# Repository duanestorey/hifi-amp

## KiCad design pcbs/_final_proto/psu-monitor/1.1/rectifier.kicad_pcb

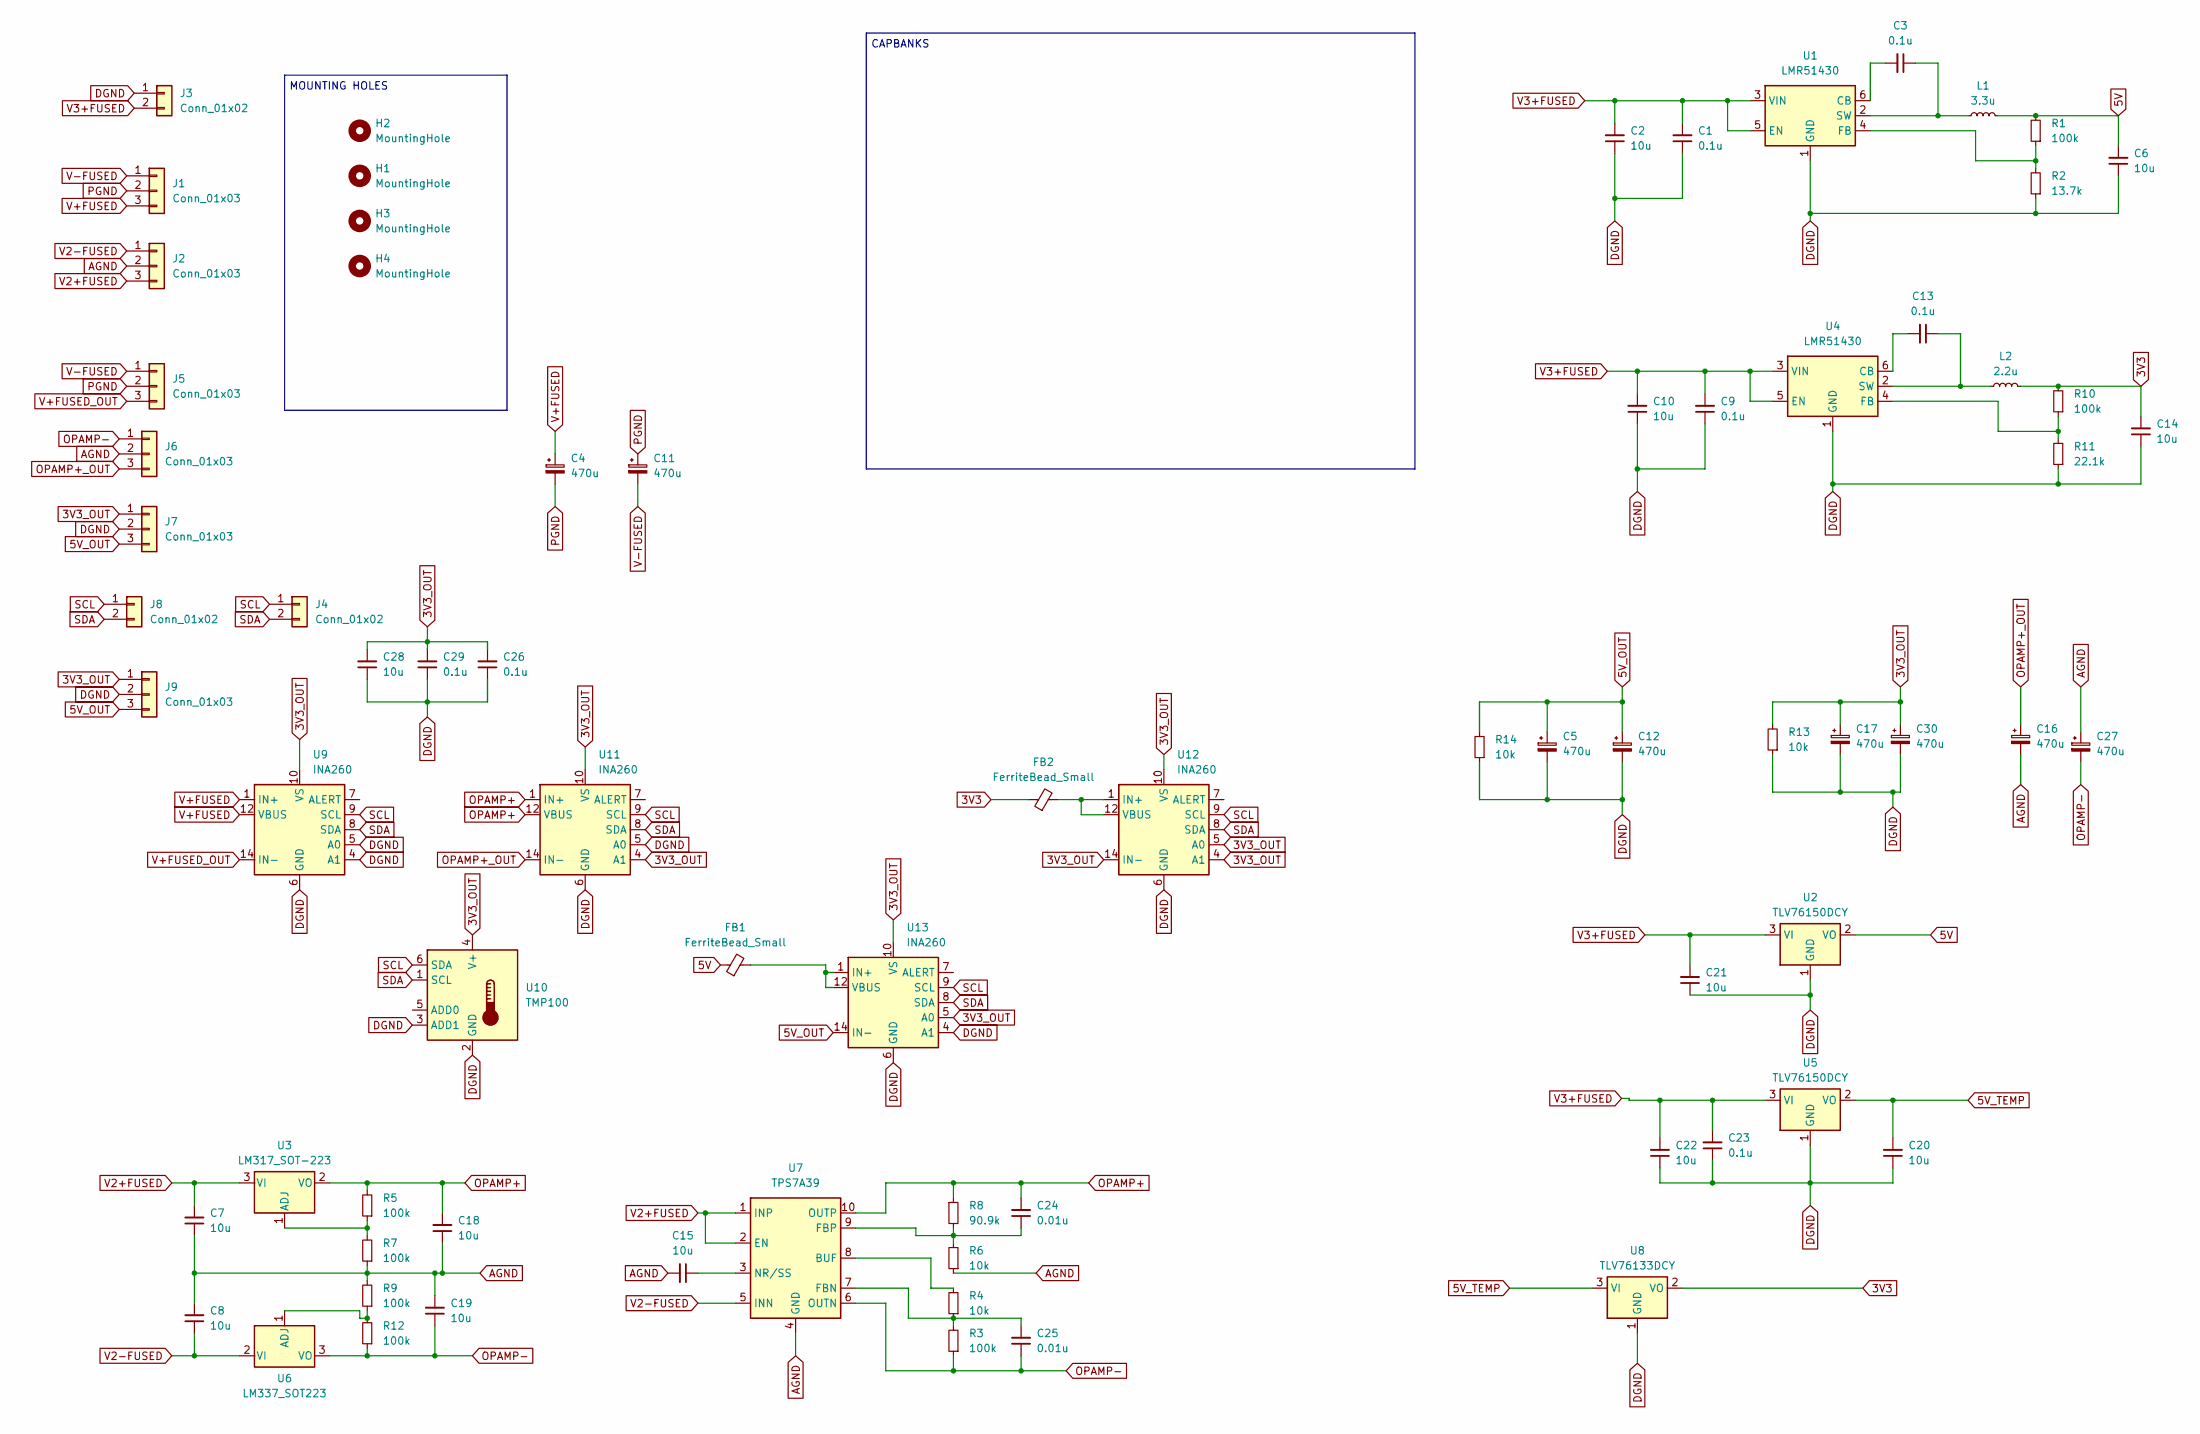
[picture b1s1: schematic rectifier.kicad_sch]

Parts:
C1, C3, C9, C13, C23, C26, C29: 0.1u; C_0805_2012Metric_Pad1.18x1.45mm_HandSolder_Duane
C2, C6, C7, C8, C10, C14, C15, C18, C19, C20, C21, C22, C28: 10u; C_1206_3216Metric_Pad1.33x1.80mm_HandSolder_Duane
C4, C5, C11, C12, C16, C17, C27, C30: 470u; CP_Elec_6.3x7.7
C24, C25: 0.01u; C_0805_2012Metric_Pad1.18x1.45mm_HandSolder_Duane
FB1, FB2: FerriteBead_Small; R_0805_2012Metric_Pad1.20x1.40mm_HandSolder_Duane
H1, H2, H3, H4: MountingHole; MountingHole_3.2mm_M3_DIN965_Pad_TopBottom
J1, J2, J5, J6, J7: Conn_01x03; JST_VH_B3P-VH-B_1x03_P3.96mm_Vertical_Duane
J3: Conn_01x02; JST_VH_B2P-VH-B_1x02_P3.96mm_Vertical_Duane
J4, J8: Conn_01x02; JST_PH_B2B-PH-K_1x02_P2.00mm_Vertical
J9: Conn_01x03; JST_PH_B3B-PH-K_1x03_P2.00mm_Vertical
L1: 3.3u; L_Wuerth_HCI-7030
L2: 2.2u; L_Wuerth_HCI-7030
R1, R3, R5, R7, R9, R10, R12: 100k; R_0805_2012Metric_Pad1.20x1.40mm_HandSolder_Duane
R2: 13.7k; R_0805_2012Metric_Pad1.20x1.40mm_HandSolder_Duane
R4, R6, R13, R14: 10k; R_0805_2012Metric_Pad1.20x1.40mm_HandSolder_Duane
R8: 90.9k; R_0805_2012Metric_Pad1.20x1.40mm_HandSolder_Duane
R11: 22.1k; R_0805_2012Metric_Pad1.20x1.40mm_HandSolder_Duane
U1, U4: LMR51430; SOT-23-6
U2, U5: TLV76150DCY; SOT-223-3_TabPin2
U3: LM317_SOT-223; SOT-223-3_TabPin2
U6: LM337_SOT223; SOT-223-3_TabPin2
U7: TPS7A39; Texas_S-PVSON-N10_ThermalVias
U8: TLV76133DCY; SOT-223-3_TabPin2
U9, U11, U12, U13: INA260; TSSOP-16_4.4x5mm_P0.65mm
U10: TMP100; SOT-23-6

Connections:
3V3: C14.2, FB2.1, L2.2, R10.2, U8.2 (VO)
3V3_OUT: C17.1, C26.2, C28.2, C29.2, C30.1, J7.1, J9.1, R13.2, U9.10 (VS), U10.4 (V+), U11.4 (A1), U11.10 (VS), U12.4 (A1), U12.5 (A0), U12.10 (VS), U12.14 (IN-), U12.15 (IN-), U12.16 (IN-), U13.5 (A0), U13.10 (VS)
5V: C6.2, FB1.1, L1.2, R1.2, U2.2 (VO)
5V_OUT: C5.1, C12.1, J7.3, J9.3, R14.2, U13.14 (IN-), U13.15 (IN-), U13.16 (IN-)
5V_TEMP: C20.2, U5.2 (VO), U8.3 (VI)
AGND: C7.1, C8.2, C15.2, C16.2, C18.1, C19.2, C27.1, J2.2, J6.2, R6.1, R7.1, R9.2, U7.4 (GND), U7.11 (GND)
DGND: C1.1, C2.1, C5.2, C6.1, C9.1, C10.1, C12.2, C14.1, C17.2, C20.1, C21.1, C22.1, C23.1, C26.1, C28.1, C29.1, C30.2, J3.1, J7.2, J9.2, R2.1, R11.1, R13.1, R14.1, U1.1 (GND), U2.1 (GND), U4.1 (GND), U5.1 (GND), U8.1 (GND), U9.4 (A1), U9.5 (A0), U9.6 (GND), U9.11 (GND), U10.2 (GND), U10.3 (ADD1), U11.5 (A0), U11.6 (GND), U11.11 (GND), U12.6 (GND), U12.11 (GND), U13.4 (A1), U13.6 (GND), U13.11 (GND)
unnamed: C3.2, U1.6 (CB)
unnamed: R1.1, R2.2, U1.4 (FB)
unnamed: C3.1, L1.1, U1.2 (SW)
unnamed: R5.1, R7.2, U3.1 (ADJ)
unnamed: C13.2, U4.6 (CB)
unnamed: R10.1, R11.2, U4.4 (FB)
unnamed: C13.1, L2.1, U4.2 (SW)
unnamed: R9.1, R12.2, U6.1 (ADJ)
unnamed: R4.2, U7.8 (BUF)
unnamed: C25.2, R3.2, R4.1, U7.7 (FBN)
unnamed: C24.1, R6.2, R8.2, U7.9 (FBP)
unnamed: C15.1, U7.3 (NR/SS)
unnamed: FB2.2, U12.1 (IN+), U12.2 (IN+), U12.3 (IN+), U12.12 (VBUS)
unnamed: FB1.2, U13.1 (IN+), U13.2 (IN+), U13.3 (IN+), U13.12 (VBUS)
OPAMP+: C18.2, C24.2, R5.2, R8.1, U3.2 (VO), U7.10 (OUTP), U11.1 (IN+), U11.2 (IN+), U11.3 (IN+), U11.12 (VBUS)
OPAMP+_OUT: C16.1, J6.3, U11.14 (IN-), U11.15 (IN-), U11.16 (IN-)
OPAMP-: C19.1, C25.1, C27.2, J6.1, R3.1, R12.1, U6.3 (VO), U7.6 (OUTN)
PGND: C4.2, C11.1, J1.2, J5.2
SCL: J4.1, J8.1, U9.9 (SCL), U10.6 (SDA), U11.9 (SCL), U12.9 (SCL), U13.9 (SCL)
SDA: J4.2, J8.2, U9.8 (SDA), U10.1 (SCL), U11.8 (SDA), U12.8 (SDA), U13.8 (SDA)
V2+FUSED: C7.2, J2.3, U3.3 (VI), U7.1 (INP), U7.2 (EN)
V2-FUSED: C8.1, J2.1, U6.2 (VI), U7.5 (INN)
V3+FUSED: C1.2, C2.2, C9.2, C10.2, C21.2, C22.2, C23.2, J3.2, U1.3 (VIN), U1.5 (EN), U2.3 (VI), U4.3 (VIN), U4.5 (EN), U5.3 (VI)
V+FUSED: C4.1, J1.3, U9.1 (IN+), U9.2 (IN+), U9.3 (IN+), U9.12 (VBUS)
V+FUSED_OUT: J5.3, U9.14 (IN-), U9.15 (IN-), U9.16 (IN-)
V-FUSED: C11.2, J1.1, J5.1

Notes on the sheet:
MOUNTING HOLES
CAPBANKS

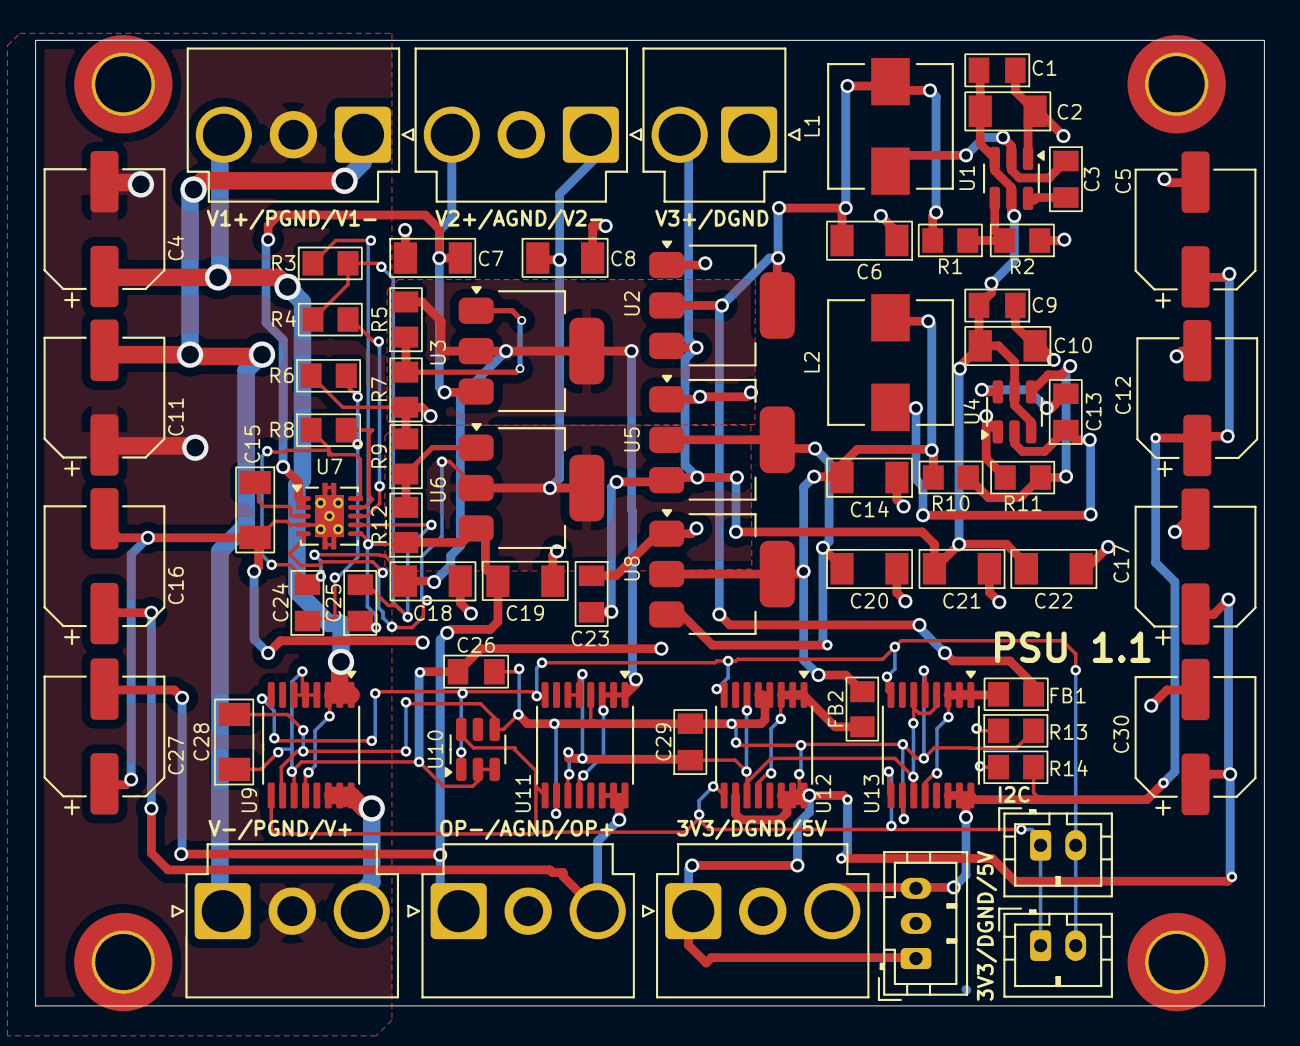
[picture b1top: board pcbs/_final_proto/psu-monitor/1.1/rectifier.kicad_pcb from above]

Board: 2 copper layers, 70.0 x 55.0 mm, 74 parts (0 on the bottom side), 33 nets.

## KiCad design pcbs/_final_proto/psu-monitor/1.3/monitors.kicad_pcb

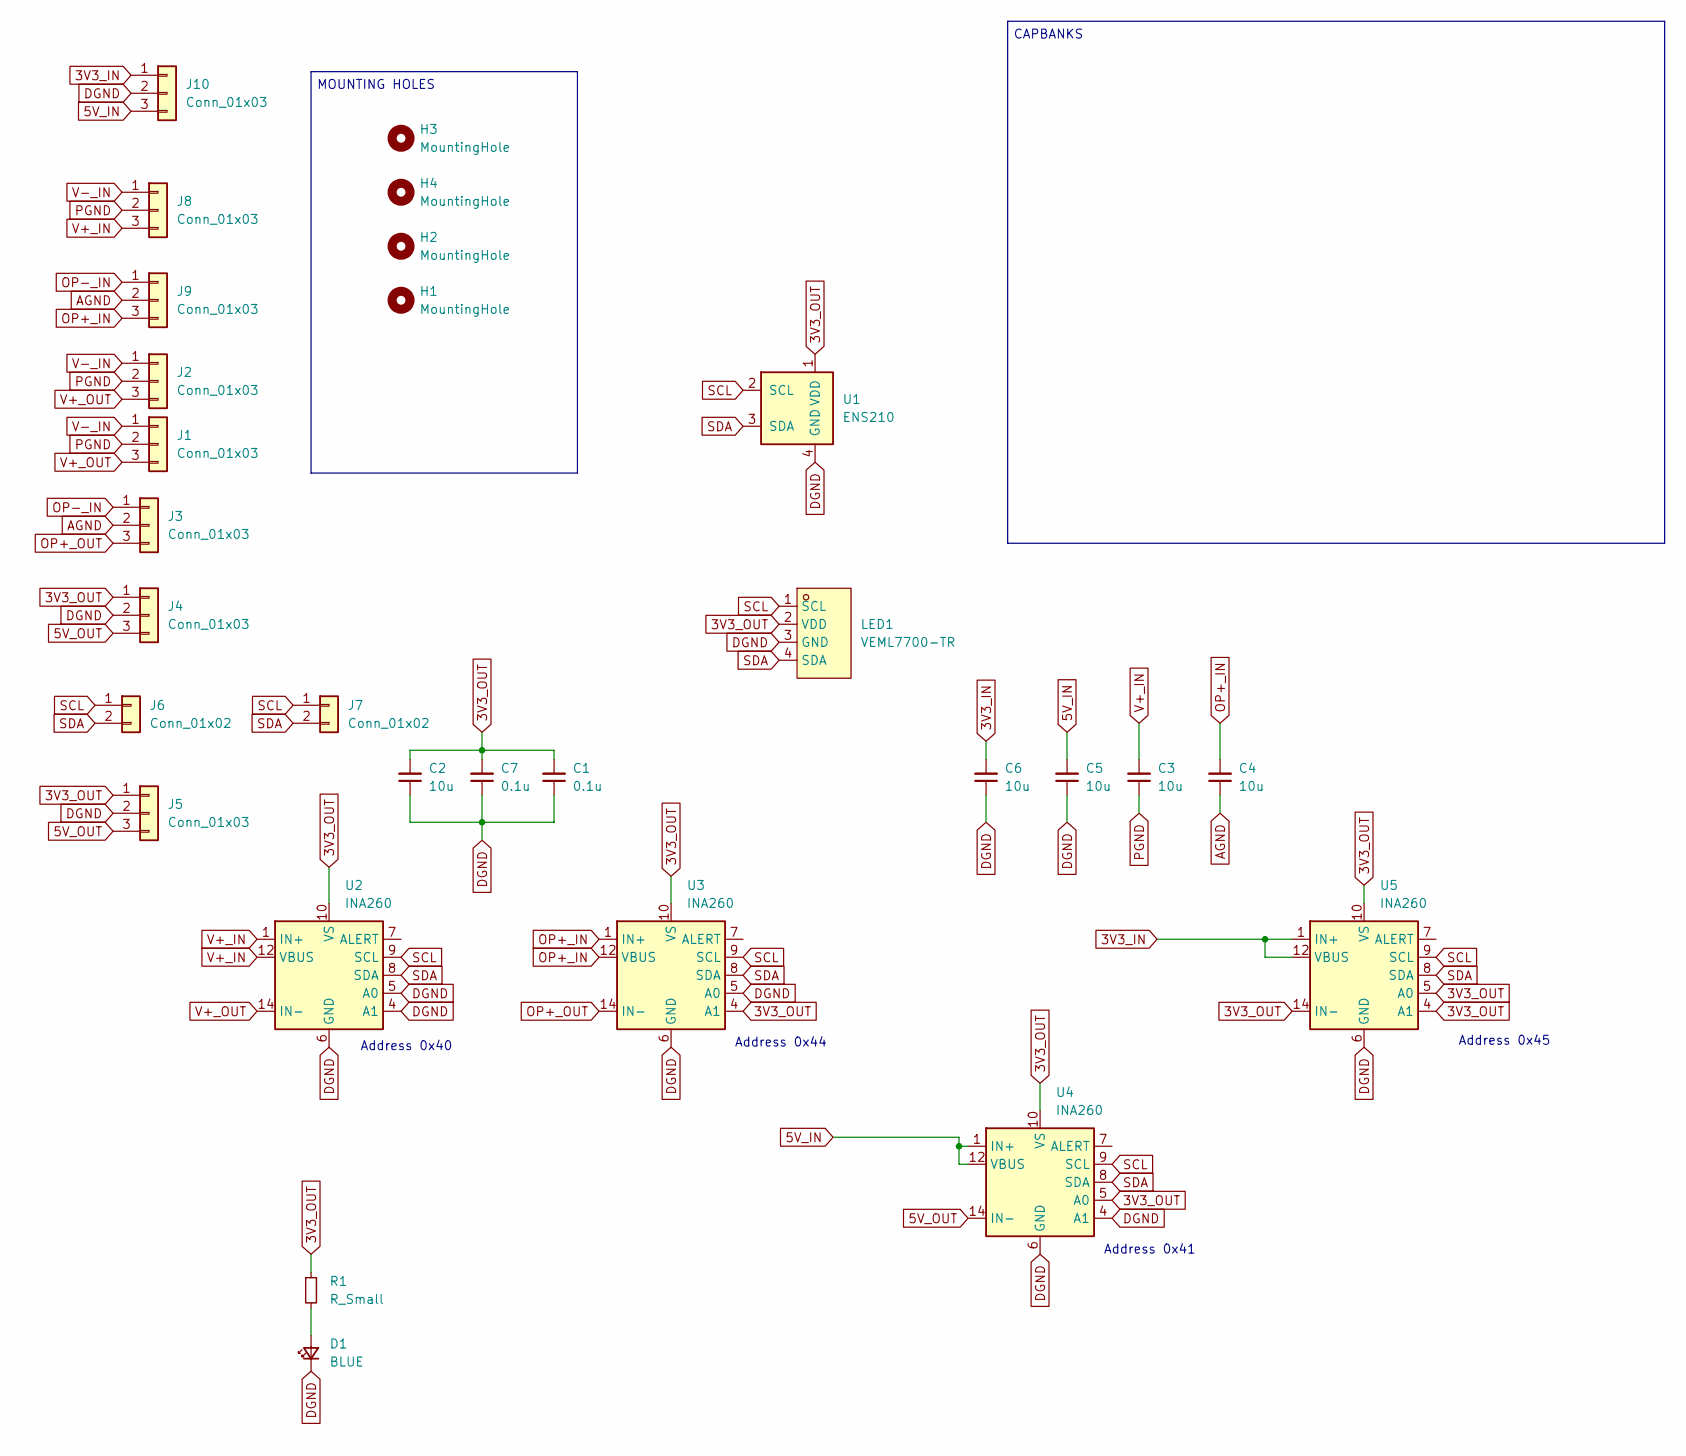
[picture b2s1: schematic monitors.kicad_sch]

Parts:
C1, C7: 0.1u; C_0805_2012Metric_Pad1.18x1.45mm_HandSolder_Duane
C2, C3, C4, C5, C6: 10u; C_1206_3216Metric_Pad1.33x1.80mm_HandSolder_Duane
D1: BLUE; LED_0805_2012Metric_Pad_HandSolder_Duane
H1, H2, H3, H4: MountingHole; MountingHole_3.2mm_M3_DIN965_Pad_TopBottom
J1, J2, J3, J4, J8, J9, J10: Conn_01x03; JST_VH_B3P-VH-B_1x03_P3.96mm_Vertical_Duane
J5: Conn_01x03; JST_PH_B3B-PH-K_1x03_P2.00mm_Vertical
J6, J7: Conn_01x02; JST_PH_B2B-PH-K_1x02_P2.00mm_Vertical
LED1: VEML7700-TR; LED-SMD_4P-L6.8-W2.4_VEML7700-TR; LCSC Part C504893
R1: R_Small; R_0805_2012Metric_Pad1.20x1.40mm_HandSolder_Duane
U1: ENS210; AMS_QFN-4-1EP_2x2mm_P0.95mm_EP0.7x1.6mm
U2, U3, U4, U5: INA260; TSSOP-16_4.4x5mm_P0.65mm

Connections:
3V3_IN: C6.2, J10.1, U5.1 (IN+), U5.2 (IN+), U5.3 (IN+), U5.12 (VBUS)
3V3_OUT: C1.2, C2.2, C7.2, J4.1, J5.1, LED1.2 (VDD), R1.1, U1.1 (VDD), U2.10 (VS), U3.4 (A1), U3.10 (VS), U4.5 (A0), U4.10 (VS), U5.4 (A1), U5.5 (A0), U5.10 (VS), U5.14 (IN-), U5.15 (IN-), U5.16 (IN-)
5V_IN: C5.2, J10.3, U4.1 (IN+), U4.2 (IN+), U4.3 (IN+), U4.12 (VBUS)
5V_OUT: J4.3, J5.3, U4.14 (IN-), U4.15 (IN-), U4.16 (IN-)
AGND: C4.1, J3.2, J9.2
DGND: C1.1, C2.1, C5.1, C6.1, C7.1, D1.1 (K), J4.2, J5.2, J10.2, LED1.3 (GND), U1.4 (GND), U1.5 (GND), U2.4 (A1), U2.5 (A0), U2.6 (GND), U2.11 (GND), U3.5 (A0), U3.6 (GND), U3.11 (GND), U4.4 (A1), U4.6 (GND), U4.11 (GND), U5.6 (GND), U5.11 (GND)
unnamed: D1.2 (A), R1.2
OP+_IN: C4.2, J9.3, U3.1 (IN+), U3.2 (IN+), U3.3 (IN+), U3.12 (VBUS)
OP+_OUT: J3.3, U3.14 (IN-), U3.15 (IN-), U3.16 (IN-)
OP-_IN: J3.1, J9.1
PGND: C3.1, J1.2, J2.2, J8.2
SCL: J6.1, J7.1, LED1.1 (SCL), U1.2 (SCL), U2.9 (SCL), U3.9 (SCL), U4.9 (SCL), U5.9 (SCL)
SDA: J6.2, J7.2, LED1.4 (SDA), U1.3 (SDA), U2.8 (SDA), U3.8 (SDA), U4.8 (SDA), U5.8 (SDA)
V+_IN: C3.2, J8.3, U2.1 (IN+), U2.2 (IN+), U2.3 (IN+), U2.12 (VBUS)
V+_OUT: J1.3, J2.3, U2.14 (IN-), U2.15 (IN-), U2.16 (IN-)
V-_IN: J1.1, J2.1, J8.1

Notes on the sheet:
Address 0x44
Address 0x41
MOUNTING HOLES
Address 0x45
CAPBANKS
Address 0x40

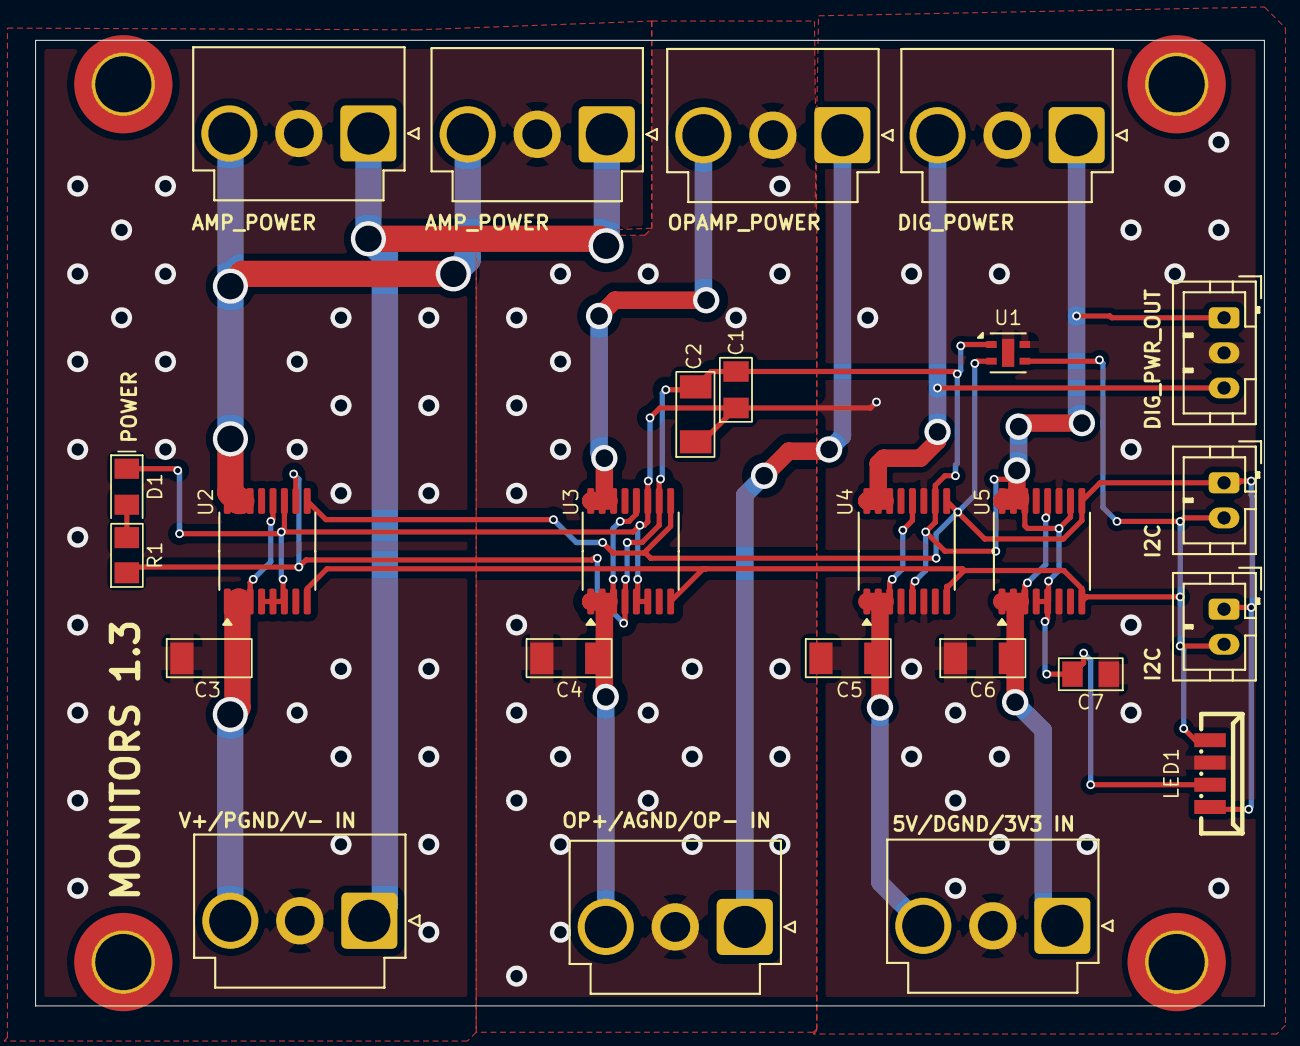
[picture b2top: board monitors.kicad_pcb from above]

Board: 2 copper layers, 70.0 x 55.0 mm, 29 parts (0 on the bottom side), 16 nets.

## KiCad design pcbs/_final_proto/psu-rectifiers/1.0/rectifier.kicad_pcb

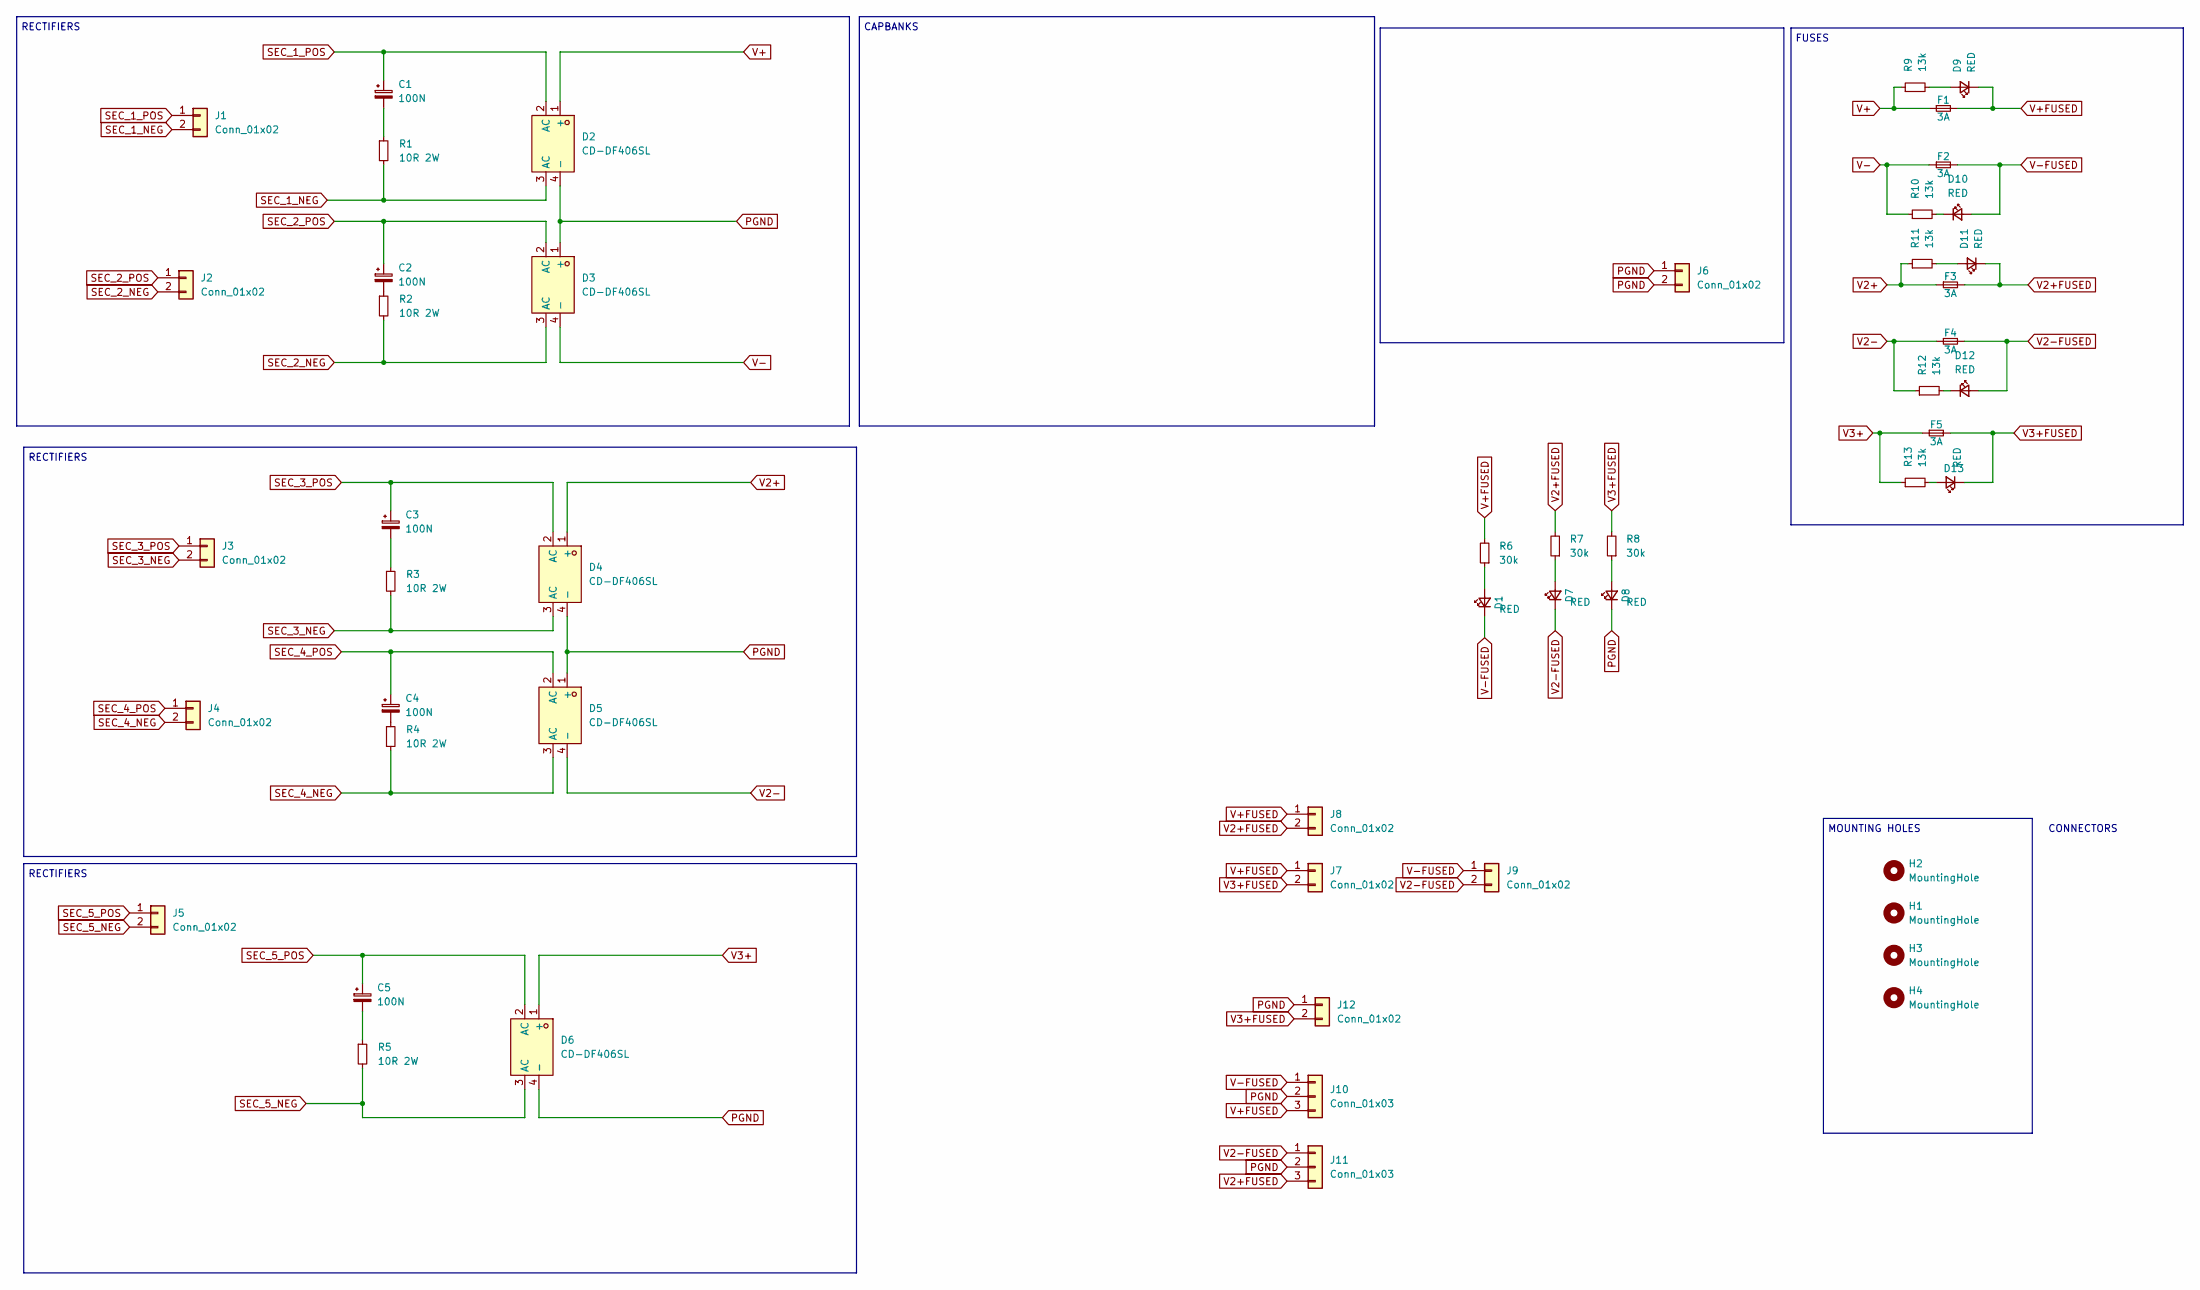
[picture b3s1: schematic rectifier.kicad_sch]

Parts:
C1, C2, C3, C4, C5: 100N; C_Rect_L10.3mm_W4.5mm_P7.50mm_MKS4; Mouser MKP4F031002D00KF00
D1, D7, D8, D9, D10, D11, D12, D13: RED; LED_0805_2012Metric_Pad_HandSolder_Duane
D2, D3, D4, D5, D6: CD-DF406SL; Z4-D_4P-L10.5-W8.1-P5.08-TL; LCSC Part C17188088
F1, F2, F3, F4, F5: 3A; Fuse_1812_AliExpress
H1, H2, H3, H4: MountingHole; MountingHole_3.2mm_M3_DIN965_Pad_TopBottom
J1, J2, J3, J4, J5, J6, J12: Conn_01x02; TerminalBlock_Phoenix_PT-1,5-2-3.5-H_1x02_P3.50mm_Horizontal
J7, J8, J9: Conn_01x02; PinHeader_1x02_P2.54mm_Vertical
J10, J11: Conn_01x03; TerminalBlock_Phoenix_PT-1,5-3-3.5-H_1x03_P3.50mm_Horizontal
R1, R2, R3, R4, R5: 10R 2W; R_2512_6332Metric_Pad1.40x3.35mm_HandSolder; Mouser 603-SR2512JK-7W10RL
R6, R7, R8: 30k; R_0805_2012Metric_Pad1.20x1.40mm_HandSolder_Duane; Mouser 603-SR2512JK-7W10RL
R9, R10, R11, R12, R13: 13k; R_0805_2012Metric_Pad1.20x1.40mm_HandSolder_Duane; Mouser 603-SR2512JK-7W10RL

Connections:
unnamed: C1.2, R1.1
unnamed: C2.2, R2.1
unnamed: C3.2, R3.1
unnamed: C4.2, R4.1
unnamed: C5.2, R5.1
unnamed: D1.2 (A), R6.1
unnamed: D7.2 (A), R7.1
unnamed: D8.2 (A), R8.1
unnamed: D9.2 (A), R9.2
unnamed: D10.1 (K), R10.2
unnamed: D11.2 (A), R11.2
unnamed: D12.1 (K), R12.2
unnamed: D13.2 (A), R13.2
PGND: D2.4 (-), D3.1 (+), D4.4 (-), D5.1 (+), D6.4 (-), D8.1 (K), J6.1, J6.2, J10.2, J11.2, J12.1
SEC_1_NEG: D2.3 (AC), J1.2, R1.2
SEC_1_POS: C1.1, D2.2 (AC), J1.1
SEC_2_NEG: D3.3 (AC), J2.2, R2.2
SEC_2_POS: C2.1, D3.2 (AC), J2.1
SEC_3_NEG: D4.3 (AC), J3.2, R3.2
SEC_3_POS: C3.1, D4.2 (AC), J3.1
SEC_4_NEG: D5.3 (AC), J4.2, R4.2
SEC_4_POS: C4.1, D5.2 (AC), J4.1
SEC_5_NEG: D6.3 (AC), J5.2, R5.2
SEC_5_POS: C5.1, D6.2 (AC), J5.1
V2+: D4.1 (+), F3.1, R11.1
V2+FUSED: D11.1 (K), F3.2, J8.2, J11.3, R7.2
V2-: D5.4 (-), F4.1, R12.1
V2-FUSED: D7.1 (K), D12.2 (A), F4.2, J9.2, J11.1
V3+: D6.1 (+), F5.1, R13.1
V3+FUSED: D13.1 (K), F5.2, J7.2, J12.2, R8.2
V+: D2.1 (+), F1.1, R9.1
V+FUSED: D9.1 (K), F1.2, J7.1, J8.1, J10.3, R6.2
V-: D3.4 (-), F2.1, R10.1
V-FUSED: D1.1 (K), D10.2 (A), F2.2, J9.1, J10.1

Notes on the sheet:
MOUNTING HOLES
RECTIFIERS
CONNECTORS
CAPBANKS
FUSES

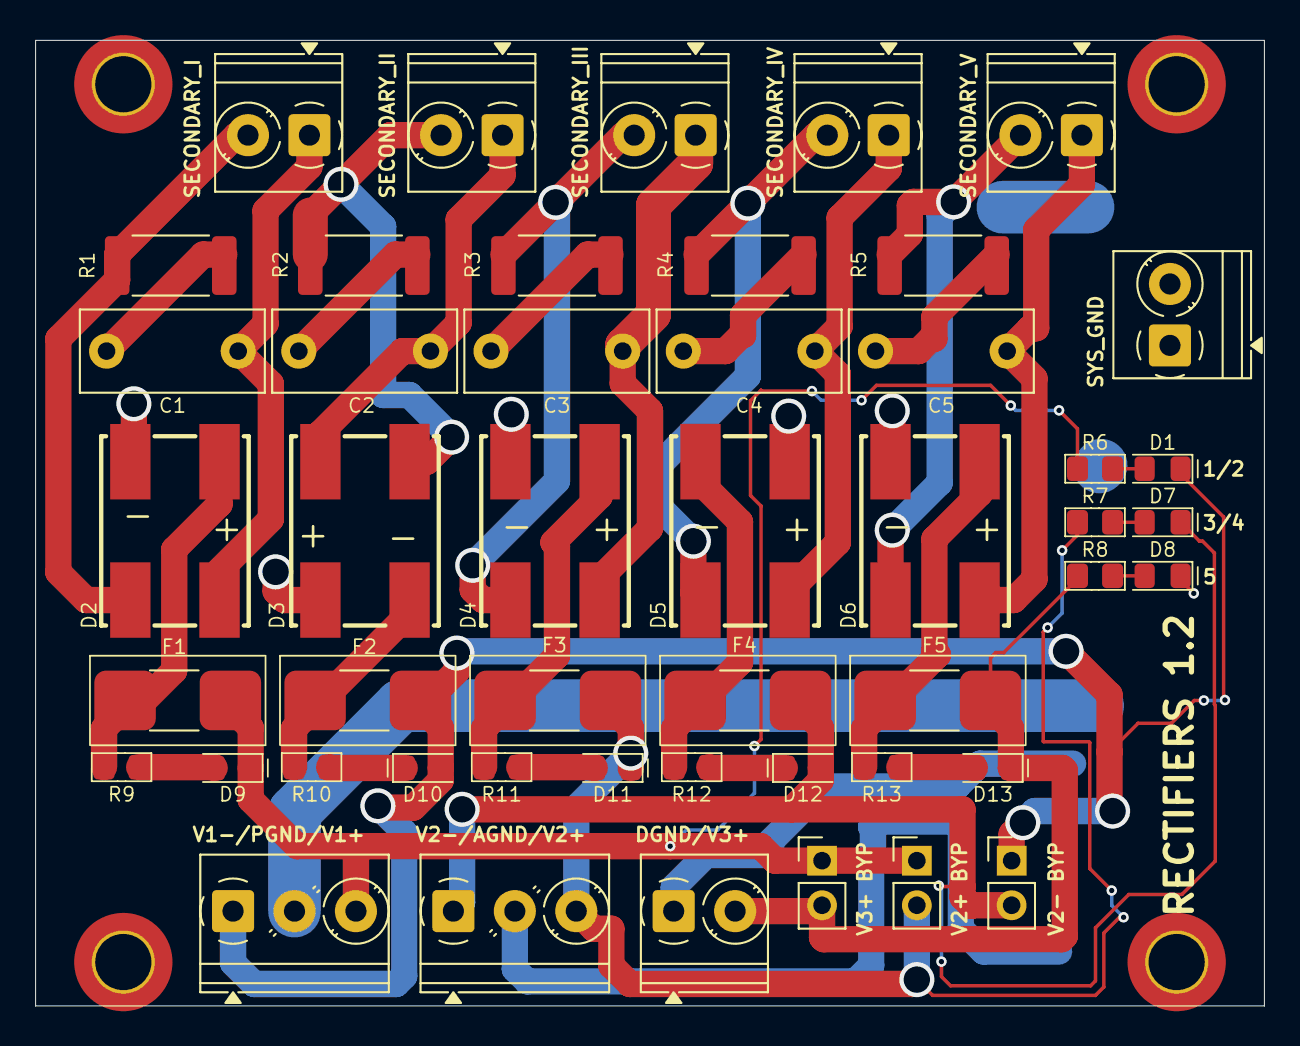
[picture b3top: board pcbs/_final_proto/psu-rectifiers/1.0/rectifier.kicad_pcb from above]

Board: 2 copper layers, 70.0 x 55.0 mm, 52 parts (0 on the bottom side), 34 nets.

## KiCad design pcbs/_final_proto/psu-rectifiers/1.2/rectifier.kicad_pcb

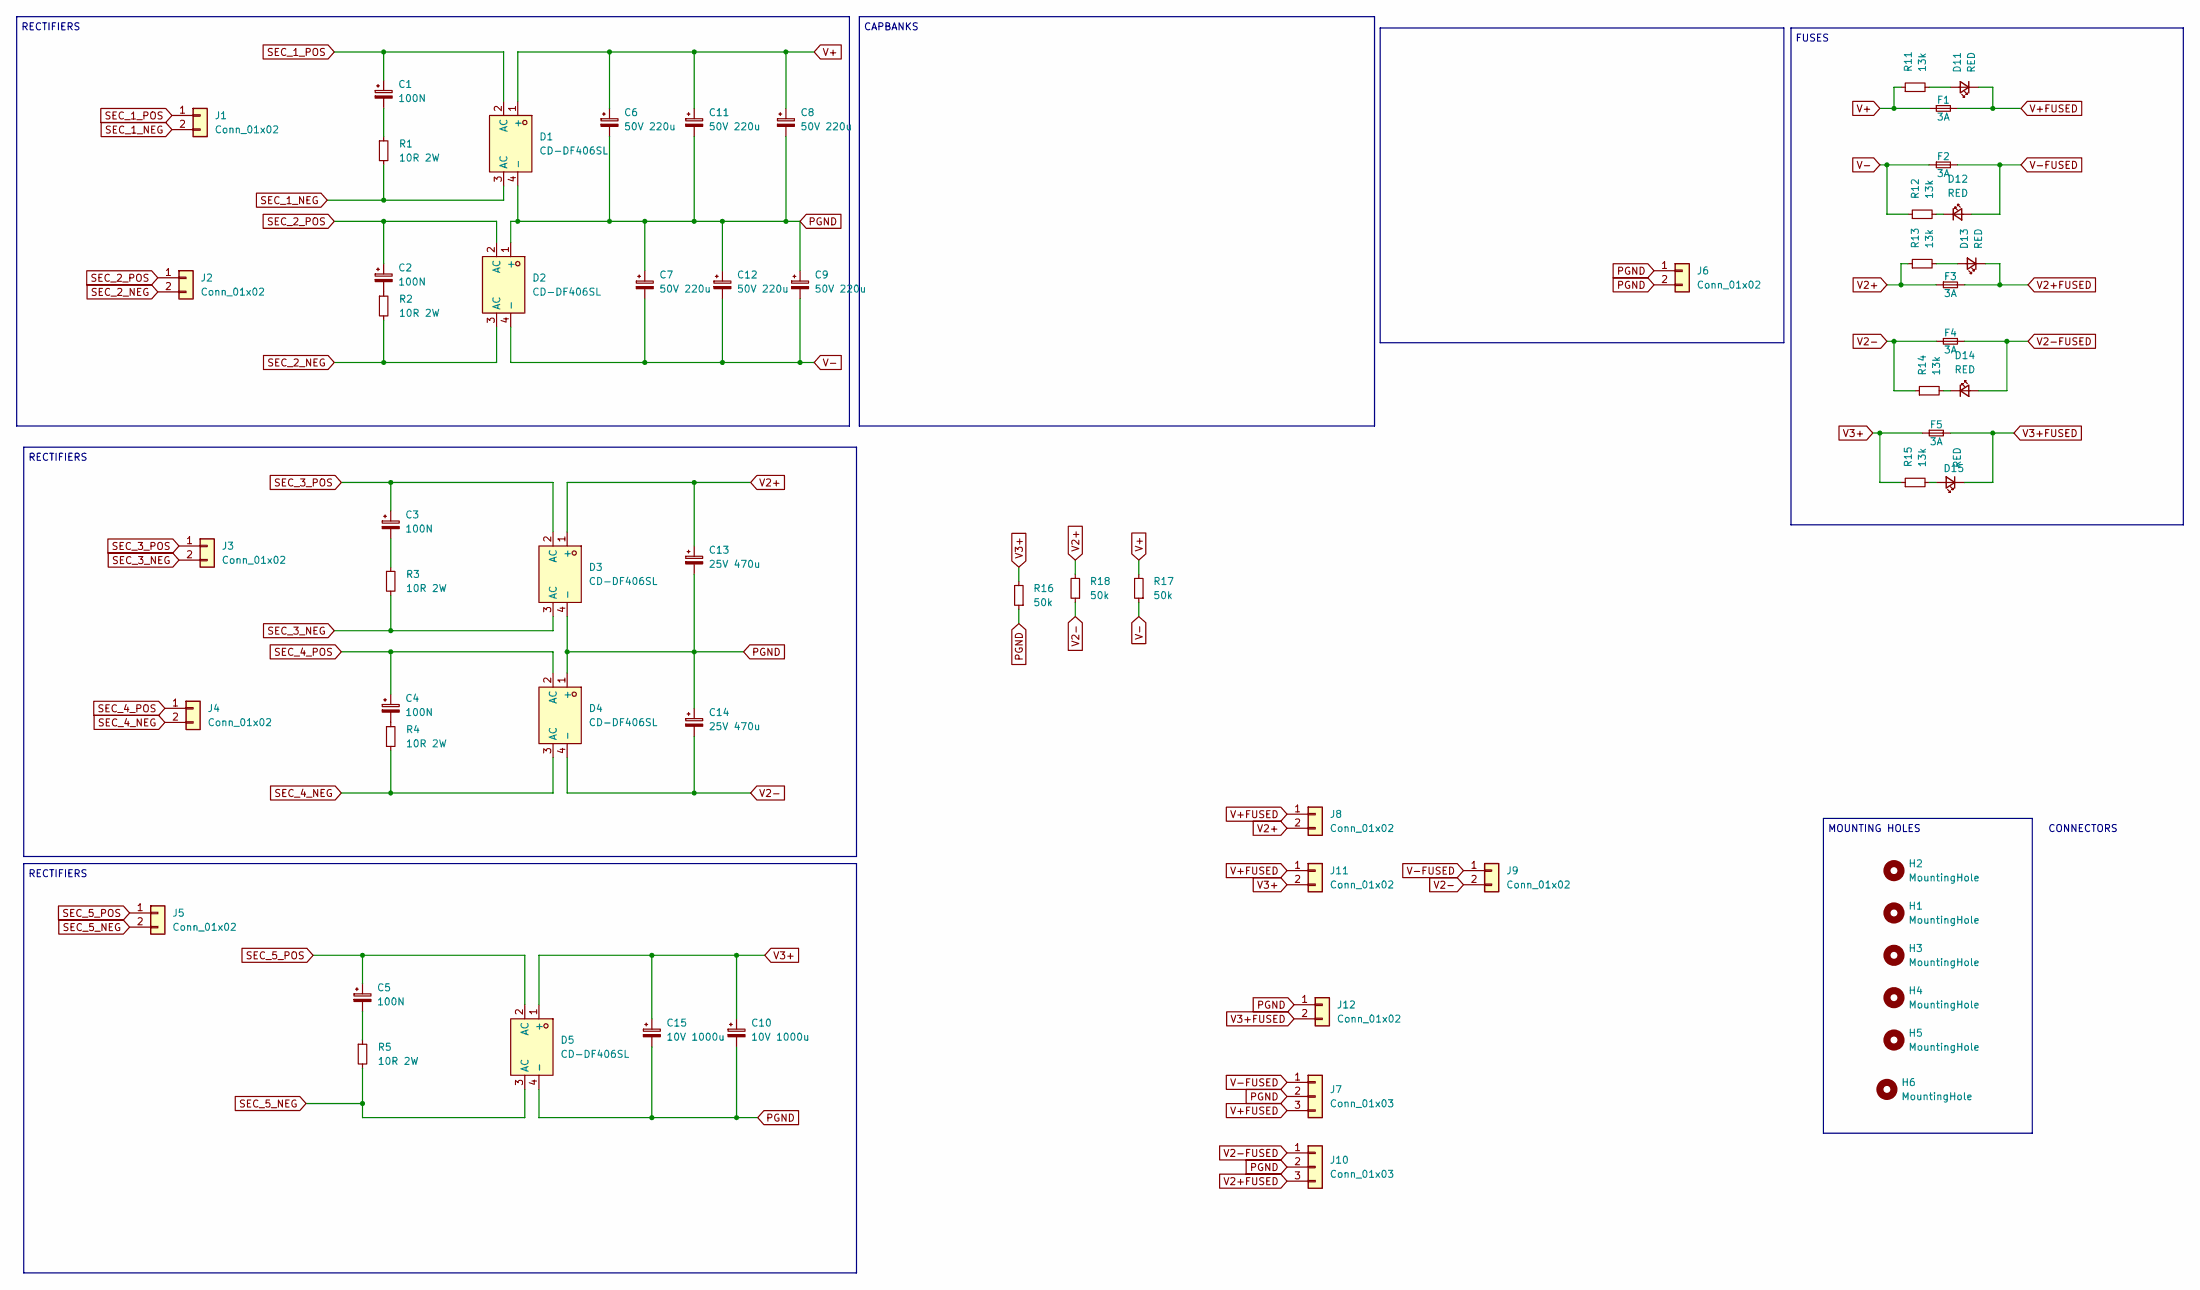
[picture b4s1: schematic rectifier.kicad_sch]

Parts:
C1, C2, C3, C4, C5: 100N; C_Rect_L10.3mm_W4.5mm_P7.50mm_MKS4; Mouser MKP4F031002D00KF00
C6, C7, C8, C9, C11, C12: 50V 220u; CP_Elec_10x10.5
C10, C15: 10V 1000u; CP_Elec_10x10.5
C13, C14: 25V 470u; CP_Elec_10x10.5
D1, D2, D3, D4, D5: CD-DF406SL; Z4-D_4P-L10.5-W8.1-P5.08-TL; LCSC Part C17188088
D11, D12, D13, D14, D15: RED; LED_0805_2012Metric_Pad_HandSolder_Duane
F1, F2, F3, F4, F5: 3A; Fuse_1812_AliExpress
H1, H2, H3, H4, H5, H6: MountingHole; MountingHole_3.2mm_M3_DIN965_Pad_TopBottom
J1, J2, J3, J4, J5, J6: Conn_01x02; JST_VH_B2P-VH-B_1x02_P3.96mm_Vertical
J7, J10: Conn_01x03; JST_VH_B3P-VH-B_1x03_P3.96mm_Vertical_Duane
J8, J9, J11: Conn_01x02; PinHeader_1x02_P2.54mm_Vertical
J12: Conn_01x02; JST_VH_B2P-VH-B_1x02_P3.96mm_Vertical_Duane
R1, R2, R3, R4, R5: 10R 2W; R_2512_6332Metric_Pad1.40x3.35mm_HandSolder; Mouser 603-SR2512JK-7W10RL
R11, R12, R13, R14, R15: 13k; R_0805_2012Metric_Pad1.20x1.40mm_HandSolder_Duane; Mouser 603-SR2512JK-7W10RL
R16, R17, R18: 50k; R_0805_2012Metric_Pad1.20x1.40mm_HandSolder_Duane; Mouser 603-SR2512JK-7W10RL

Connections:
unnamed: C1.2, R1.1
unnamed: C2.2, R2.1
unnamed: C3.2, R3.1
unnamed: C4.2, R4.1
unnamed: C5.2, R5.1
unnamed: D11.2 (A), R11.2
unnamed: D12.1 (K), R12.2
unnamed: D13.2 (A), R13.2
unnamed: D14.1 (K), R14.2
unnamed: D15.2 (A), R15.2
PGND: C6.2, C7.1, C8.2, C9.1, C10.2, C11.2, C12.1, C13.2, C14.1, C15.2, D1.4 (-), D2.1 (+), D3.4 (-), D4.1 (+), D5.4 (-), J6.1, J6.2, J7.2, J10.2, J12.1, R16.1
SEC_1_NEG: D1.3 (AC), J1.2, R1.2
SEC_1_POS: C1.1, D1.2 (AC), J1.1
SEC_2_NEG: D2.3 (AC), J2.2, R2.2
SEC_2_POS: C2.1, D2.2 (AC), J2.1
SEC_3_NEG: D3.3 (AC), J3.2, R3.2
SEC_3_POS: C3.1, D3.2 (AC), J3.1
SEC_4_NEG: D4.3 (AC), J4.2, R4.2
SEC_4_POS: C4.1, D4.2 (AC), J4.1
SEC_5_NEG: D5.3 (AC), J5.2, R5.2
SEC_5_POS: C5.1, D5.2 (AC), J5.1
V2+: C13.1, D3.1 (+), F3.1, J8.2, R13.1, R18.2
V2+FUSED: D13.1 (K), F3.2, J10.3
V2-: C14.2, D4.4 (-), F4.1, J9.2, R14.1, R18.1
V2-FUSED: D14.2 (A), F4.2, J10.1
V3+: C10.1, C15.1, D5.1 (+), F5.1, J11.2, R15.1, R16.2
V3+FUSED: D15.1 (K), F5.2, J12.2
V+: C6.1, C8.1, C11.1, D1.1 (+), F1.1, R11.1, R17.2
V+FUSED: D11.1 (K), F1.2, J7.3, J8.1, J11.1
V-: C7.2, C9.2, C12.2, D2.4 (-), F2.1, R12.1, R17.1
V-FUSED: D12.2 (A), F2.2, J7.1, J9.1

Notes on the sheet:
MOUNTING HOLES
RECTIFIERS
CONNECTORS
CAPBANKS
FUSES
